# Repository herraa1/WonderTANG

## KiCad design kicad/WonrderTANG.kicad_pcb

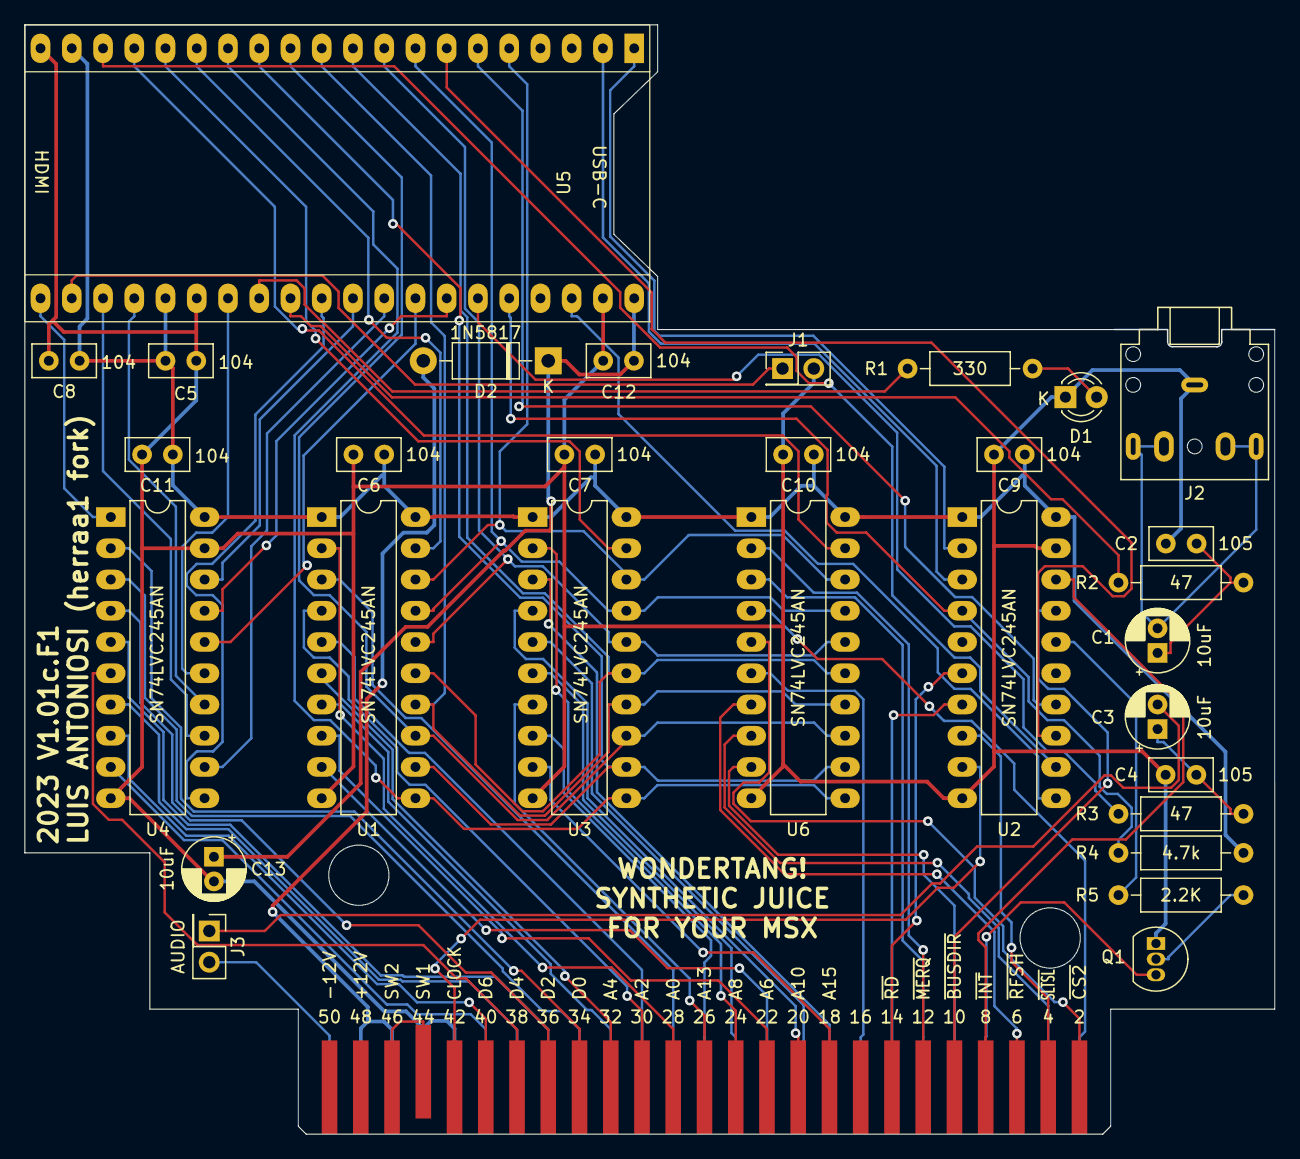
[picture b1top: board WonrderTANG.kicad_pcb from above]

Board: 2 copper layers, 101.6 x 90.2 mm, 31 parts (0 on the bottom side), 83 nets.

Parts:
C1, C3, C13: 10uF; CP_Radial_D5.0mm_P2.00mm
C2, C4: 105; C_Disc_D5.0mm_W2.5mm_P2.50mm
C5, C6, C7, C8, C9, C10, C11, C12: 104; C_Disc_D5.0mm_W2.5mm_P2.50mm
CON1: MSX-CONNECTOR; CARTRIDGE_MSX
D1: LED; LED_D3.0mm
D2: 1N5817; D_DO-41_SOD81_P10.16mm_Horizontal
J1, J3: Conn_02x01; PinHeader_2x01_P2.54mm_Vertical
J2: AudioJack3; Jack_3.5mm_CUI_SJ1-3525N_Horizontal
Q1: 2N3904; TO-92_Inline
R1: 330; R_Axial_DIN0207_L6.3mm_D2.5mm_P10.16mm_Horizontal
R2, R3: 47; R_Axial_DIN0207_L6.3mm_D2.5mm_P10.16mm_Horizontal
R4: 4.7k; R_Axial_DIN0207_L6.3mm_D2.5mm_P10.16mm_Horizontal
R5: 2.2K; R_Axial_DIN0207_L6.3mm_D2.5mm_P10.16mm_Horizontal
U1, U2, U3, U4, U6: SN74LVC245AN; DIP-20_W7.62mm_LongPads
U5: Tang_Nano_20k

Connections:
+3.3V: C5.1, C6.1, C7.1, C8.1, C9.1, C10.1, C11.1, R4.1, U1.1 (A->B), U1.20 (VCC), U2.1 (A->B), U2.20 (VCC), U3.1 (A->B), U3.20 (VCC), U4.20 (VCC), U5.19 (3V3), U5.25 (3V3), U6.1 (A->B), U6.20 (VCC)
+5V: C12.1, C13.1, D2.1 (K), U5.40 (5V)
/CART_5V: CON1.45 (5V@1), CON1.47 (5V@2), D2.2 (A)
/WAIT_SW: R5.1, U2.16 (B2)
A0: CON1.28 (A0), U1.2 (A0)
A1: CON1.27 (A1), U1.3 (A1)
A2: CON1.30 (A2), U1.4 (A2)
A3: CON1.29 (A3), U1.5 (A3)
A4: CON1.32 (A4), U1.6 (A4)
A5: CON1.31 (A5), U1.7 (A5)
A6: CON1.22 (A6), U1.8 (A6)
A7: CON1.21 (A7), U1.9 (A7)
A8: CON1.24 (A8), U3.2 (A0)
A9: CON1.17 (A9), U3.3 (A1)
A10: CON1.20 (A10), U3.4 (A2)
A11: CON1.19 (A11), U3.5 (A3)
A12: CON1.23 (A12), U3.6 (A4)
A13: CON1.26 (A13), U3.7 (A5)
A14: CON1.25 (A14), U3.8 (A6)
A15: CON1.18 (A15), U3.9 (A7)
AUDIO_33: R3.1, U5.35 (41_IOB43A)
BUSDIR: CON1.10 (~BUSDIR), U2.17 (B1)
BUSDIR_33: U2.3 (A1), U5.2 (74_IOT34B)
CLOCK: CON1.42 (CLOCK), U2.9 (A7)
CLOCK_33: U2.11 (B7), U5.38 (76_IOT30B)
CS1: CON1.1 (~CS1), U6.4 (A2)
CS2: CON1.2 (~CS2), U6.5 (A3)
CS12: CON1.3 (~CS12), U6.8 (A6)
D0: CON1.34 (D0), U4.2 (A0)
D0_33: U4.18 (B0), U5.31 (48_IOR49B)
D1: CON1.33 (D1), U4.3 (A1)
D1_33: U4.17 (B1), U5.34 (56_IOR36A)
D2: CON1.36 (D2), U4.4 (A2)
D2_33: U4.16 (B2), U5.33 (54_IOR38A)
D3: CON1.35 (D3), U4.5 (A3)
D3_33: U4.15 (B3), U5.27 (79_IOT27B)
D4: CON1.38 (D4), U4.6 (A4)
D4_33: U4.14 (B4), U5.24 (72_IOT40B)
D5: CON1.37 (D5), U4.7 (A5)
D5_33: U4.13 (B5), U5.23 (71_IOT44A)
D6: CON1.40 (D6), U4.8 (A6)
D6_33: U4.12 (B6), U5.32 (51_IOR45A)
D7: CON1.39 (D7), U4.9 (A7)
D7_33: U4.11 (B7), U5.30 (55_IOR36B)
DATADIR: U4.1 (A->B), U5.21 (52_IOR39A)
GND: C2.2, C4.2, C5.2, C6.2, C7.2, C8.2, C9.2, C10.2, C11.2, C12.2, C13.2, CON1.41 (GND@1), CON1.43 (GND@2), D1.1 (K), J1.2, J2.S, Q1.1 (E), U1.10 (GND), U2.10 (GND), U2.19 (CE), U3.10 (GND), U4.10 (GND), U4.19 (CE), U5.20 (GND), U5.26 (GND), U5.39 (GND), U6.10 (GND)
INT: CON1.8 (~INT), U2.18 (B0)
INT_33: U2.2 (A0), U5.1 (73_IOT40A)
IORQ: CON1.11 (~IORQ), U6.3 (A1)
JP: J1.1, U5.22 (53_IOR38B)
LED: R1.1, U5.28 (86_IOT4A)
M1: CON1.9 (M1), U6.9 (A7)
MERQ: CON1.12 (~MERQ), U6.2 (A0)
MP0_33: U1.18 (B0), U3.18 (B0), U5.5 (77_IOT30A), U6.18 (B0)
MP1_33: U1.17 (B1), U3.17 (B1), U5.8 (27_IOB8A), U6.17 (B1)
MP2_33: U1.16 (B2), U3.16 (B2), U5.9 (28_IOB8B), U6.16 (B2)
MP3_33: U1.15 (B3), U3.15 (B3), U5.10 (25_IOB6A), U6.15 (B3)
MP4_33: U1.14 (B4), U3.14 (B4), U5.11 (26_IOB6B), U6.14 (B4)
MP5_33: U1.13 (B5), U3.13 (B5), U5.12 (29_IOB14A), U6.13 (B5)
MP6_33: U1.12 (B6), U3.12 (B6), U5.13 (30_IOB14B), U6.12 (B6)
MP7_33: U1.11 (B7), U3.11 (B7), U5.14 (31_IOB29A), U6.11 (B7)
MSEL0_33: U1.19 (CE), U5.15 (17_IOL49A_LED2)
MSEL1_33: U3.19 (CE), U5.16 (20_IOL51B_LED5)
MSEL2_33: U5.17 (19_IOL51A_LED4), U6.19 (CE)
unnamed: C1.1, C2.1, R2.2
unnamed: C1.2, J2.R, J2.RN, J2.T, J2.TN
unnamed: C3.1, C4.1, R3.2
unnamed: CON1.44 (SW1), CON1.46 (SW2)
unnamed: D1.2 (A), R1.2
unnamed: C3.2, J3.1
unnamed: Q1.2 (B), R5.2
RD: CON1.14 (~RD), U2.6 (A4)
RD_33: U2.14 (B4), U5.6 (15_IOL47A_LED0)
RESET: CON1.15 (~RESET), U6.6 (A4)
RFSH: CON1.6 (~RFSH), U6.7 (A5)
SLTSL: CON1.4 (~SLTSL), U2.8 (A6)
SLTSL_33: U2.12 (B6), U5.18 (18_IOL49B_LED3)
SOUNDIN: CON1.49 (SOUNDIN), J3.2
SOUND_33: R2.1, U5.29 (49_IOR49A)
WAIT: CON1.7 (/WAIT), Q1.3 (C)
WAIT_33: R4.2, U2.4 (A2), U5.36 (42_IOB42B)
WR: CON1.13 (~WR), U2.7 (A5)
WR_33: U2.13 (B5), U5.7 (16_IOL47B_LED1)

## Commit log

2023-11-19 [kicad] Fix board edge clearance violation errors
    PCB edge connectors pad types are currently declared as SMD instead of
    Edge Connector which causes 49 board edge clearance violation errors
    when running the DRC (Design Rules Checker).
    Fix those by declaring the edge connectors pad types as Edge Connector.
2023-11-19 [kicad] Fix CARTRIDGE_MSX footprint board edge clearance violation errors
    PCB edge connectors pad types are currently declared as SMD instead of
    Edge Connector which causes 49 board edge clearance violation errors
    when running the DRC (Design Rules Checker).
    Fix those by declaring the edge connectors pad types as Edge Connector.
2023-11-19 [kicad] Fix silkscreen overlap between Q1 and R5
2023-11-19 [kicad] Fix text thickness out of range errors for U5
    Fixes text thickness out of range errors for "HDMI"
    and "USB-C" texts of U5 by increasing text thickness
    from 0.1 to 0.15.
2023-11-19 [kicad] Fix silkscreen clipped by solder mask for cartridge pads
    Text for pads 3 "CS12" and 4 "SLTSL" fall within one of the holes
    used to fix the cartridge board to the cartridge case.
    Make those texts visible again by reducing text width so that they
    do not extend into the cartridge board hole.
2023-11-19 [kicad] show value for U4
    All SN74LVC245AN footprints show its value except U4.
    Fix that by adding its value to the silkscreen layer.
2023-11-19 [kicad] Use alternate audio connector SJ1-3525N
    Exchange the SJ1-3533NG mono audio connector with the more common
    (at least in Europe and some large asian shops) SJ1-3525N stereo
    connector, keeping the same orientation.
    To fit the new connector the board led is slightly moved too.
2023-11-19 [kicad] Mark board as F1 fork
    Identify this board as a new fork to avoid confusion with the stock
    board by slightly changing the silkscreen identification.
2023-11-29 Release 2023 V1.01b.F1
    Add copper planes for final fabrication.
2024-04-28 [kicad] Silkscreen updates for cartridge pads
    Mark active low signals BDIR,CS1,CS2,CS12,INT,IRQ,M1,MRQ,RD,RFSH,RST,SLTSL,WAIT,WR with a bar above them.
    Add voltage suffix V to +5, +12 and -12 signals.
    Add pad number to pad 43.
    Add pad number to pad 44.
    Name each SW pad with its own names SW1 and SW2.
    Rename BDIR to BUSDIR.
2024-04-28 [kicad] Fix /CART_5V net width
    Update the PCB to bring /CART_5V in sync with the schematic.
    Apply the power netclass width to /CART_5V as it is currently using a
    smaller width than the rest of power nets (from the cartridge pads to the
    D2 diode).
    Add clearance when needed to account for the increase in net width.
2024-04-28 [kicad] Use alternate audio connector SJ1-3525N
    Exchange the SJ1-3533NG mono audio connector with the more common
    (at least in Europe and some large asian shops) SJ1-3525N stereo
    connector, keeping the same orientation.
    To fit the new connector the board led is slightly moved too.
    This modification also allows to keep the audio connector within
    the standard cartridge case depth.
2024-04-28 [kicad] Add copper fill for GND
    Add copper fill on the bottom layer for GND.
    It may provide added signal integrity.
2024-04-28 [kicad] Mark board as V1.01c.F1 fork
    Identify this board as a new fork to avoid confusion with the stock
    board by slightly changing the silkscreen identification.
2024-05-13 test: disable all but nextor bios and sd
2024-05-14 test: enable modular build
2024-06-13 fpga: reverse int_n logic for board V1.02d and build bitstream
2024-06-17 test using jt2413
2024-06-17 re-build bitstream for V1.02d with latest changes
